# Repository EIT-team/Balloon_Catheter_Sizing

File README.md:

# Balloon Catheter Sizing

Software and firmware for "Lumen Shape Reconstruction using a Soft Robotic Balloon Catheter and Electrical Impedance Tomography" as presented at IROS 2022 [figshare](https://doi.org/10.6084/m9.figshare.16784038) or [arxiv](https://arxiv.org/abs/2207.12536)

## Requirements

- MATLAB tested only with >2019b
- [EIDORS](http://eidors3d.sourceforge.net/) - for forward modelling and absolute solvers
- [gmsh](https://gmsh.info/) - for meshing CAD files drawings
- [meshio2matlab](https://github.com/Jimbles/meshio2matlab) - to write VTU files and load gmsh files into matlab
- [Reconstruction](https://github.com/EIT-team/Reconstruction) - MATLAB library with cross validated Tikhonov 0 EIT solvers
- [ElikoQuadraMatlab](https://github.com/Jimbles/ElikoQuadra) - Library to load Eliko Quadra data
- [MS5903 Library](https://github.com/sparkfun/SparkFun_MS5803-14BA_Breakout_Arduino_Library) - for the pressure sensor
- [uStepper S-Lite](https://github.com/uStepper/uStepper-S-lite) - library for the [uStepper S-lite](https://ustepper.com/store/ustepper-boards/26-ustepper-s-lite.html) motor board for the syringe pump

## Folder overview

- [Cristina Masters](/Cristina_Masters/) - Files for Cristina's Masters and [conference paper](https://zenodo.org/record/4940249) 
- [hardware](/hardware/) - CAD files for Catheter and FPC, Arduino Motor controllers
- [numerical_analysis](/numerical_analysis/) - Scripts for analysis of the optimal electrode configuration
- [imaging](/imaging/) - Scripts to generate EIT images

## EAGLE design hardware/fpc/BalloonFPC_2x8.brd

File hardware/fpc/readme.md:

# Flexible Circuit Board

FPC with electrodes for EIT measurements, and jumper board for connecting to the Eliko Quadra

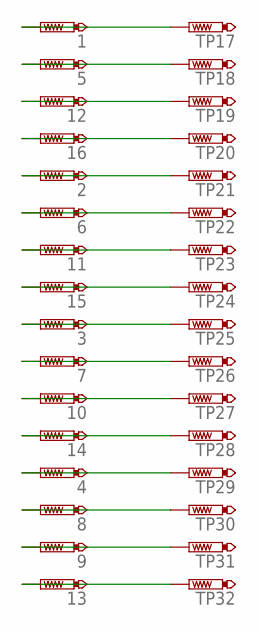
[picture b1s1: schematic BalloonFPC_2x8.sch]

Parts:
1, 2, 3, 4, 5, 6, 7, 8, 9, 10, 11, 12, 13, 14, 15, 16: PTR11X2MM; ELECPAD
TP17, TP18, TP19, TP20, TP21, TP22, TP23, TP24, TP25, TP26, TP27, TP28, TP29, TP30, TP31, TP32: PTR1ZIF; ZIFPAD

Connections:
1: 1.TP, TP17.TP
2: 2.TP, TP21.TP
3: 3.TP, TP25.TP
4: 4.TP, TP29.TP
5: 5.TP, TP18.TP
6: 6.TP, TP22.TP
7: 7.TP, TP26.TP
8: 8.TP, TP30.TP
9: 9.TP, TP31.TP
10: 10.TP, TP27.TP
11: 11.TP, TP23.TP
12: 12.TP, TP19.TP
13: 13.TP, TP32.TP
14: 14.TP, TP28.TP
15: 15.TP, TP24.TP
16: 16.TP, TP20.TP

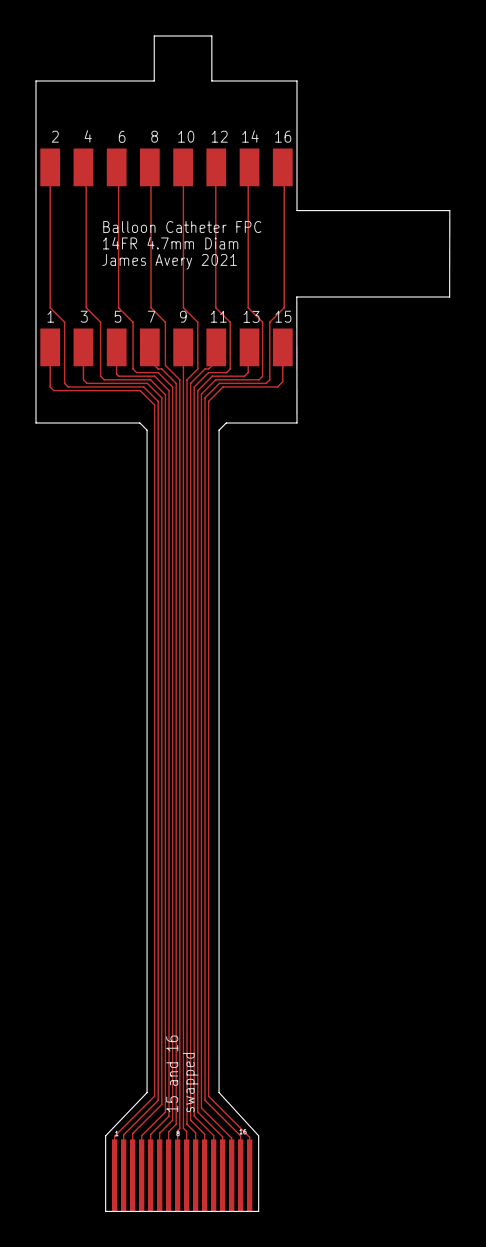
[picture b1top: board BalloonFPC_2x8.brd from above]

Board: 2 copper layers, 23.0 x 65.3 mm, 32 parts (0 on the bottom side), 16 nets.

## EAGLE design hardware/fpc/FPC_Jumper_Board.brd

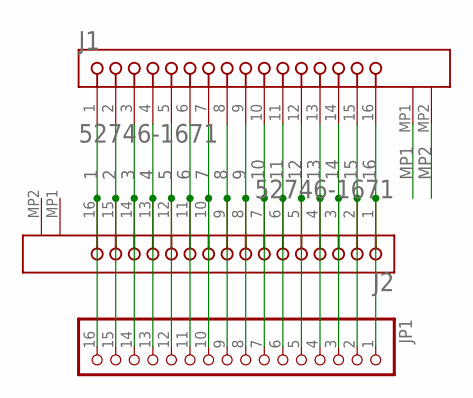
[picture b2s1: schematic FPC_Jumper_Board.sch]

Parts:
J1, J2: MOLEX_52746-1671MOLEX_52746-1671_0_0; MOLEX_52746-1671_0
JP1: PINHD-1X16; 1X16

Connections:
1: J1.1, J2.16, JP1.16
2: J1.2, J2.15, JP1.15
3: J1.3, J2.14, JP1.14
4: J1.4, J2.13, JP1.13
5: J1.5, J2.12, JP1.12
6: J1.6, J2.11, JP1.11
7: J1.7, J2.10, JP1.10
8: J1.8, J2.9, JP1.9
9: J1.9, J2.8, JP1.8
10: J1.10, J2.7, JP1.7
11: J1.11, J2.6, JP1.6
12: J1.12, J2.5, JP1.5
13: J1.13, J2.4, JP1.4
14: J1.14, J2.3, JP1.3
15: J1.15, J2.2, JP1.2
16: J1.16, J2.1, JP1.1
MP1: J1.MP1
MP2: J1.MP2

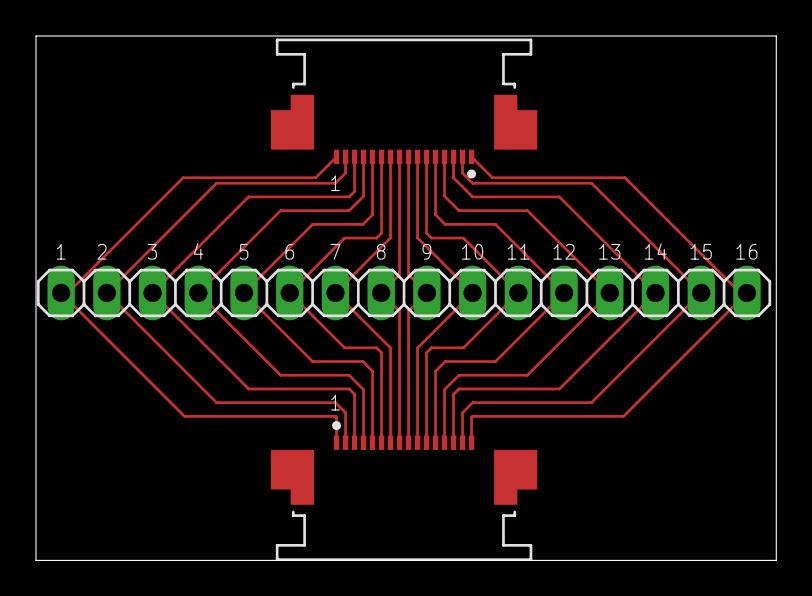
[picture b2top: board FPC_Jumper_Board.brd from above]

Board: 2 copper layers, 41.1 x 29.1 mm, 3 parts (0 on the bottom side), 16 nets.

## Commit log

2021-04-13 Create test
2021-04-13 Create test2
2021-04-13 Create test1
2021-04-19 Rename final_3D_reconstruction_point_elec.m to point_3D_abs_reconstruction.m
2021-04-19 Rename point_elec_reconstr_loop_fullplots.m to final_point_elec_3Dabsreconstr_loop_fullplots.m
2021-04-19 Rename point_elec_reconstr_loop_slices_plots.m to final_point_elec_3Dabsreconstr_loop_slices_plots.m
2022-03-15 Inital release for IROS 2022
2022-09-23 Updated links to paper
